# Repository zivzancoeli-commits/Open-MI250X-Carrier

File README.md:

# Open MI250X Carrier

## Purpose
This project collects public evidence needed to design a minimal open-source carrier board for surplus AMD Instinct MI250X OAM modules. It is organized as a reverse-engineering knowledge base: public documentation is collected first, facts are extracted into notes, and unknown or proprietary behavior is tracked instead of assumed.

Agent standing rules: [AGENTS.md](AGENTS.md). Do not invent pins. Do not send in-repo KiCad to PCBWay. Do not energize OAMs. Host / desk / SendCutSend sheet are OK to buy; wait on Molex 2189101115 60 V / skip-pin.

## Workflow
- Collect public links and local reference copies in [02_AMD_Docs](02_AMD_Docs/) and [13_Reference_Docs](13_Reference_Docs/).
- Extract design-relevant facts into [09_AI_Notes](09_AI_Notes/), separating verified information from questions.
- Use research in [08_Research_Papers](08_Research_Papers/) to understand topology, bandwidth, and system context before design decisions.
- Carry verified mechanical, PCIe, power, cooling, firmware, and software assumptions into schematic, layout, prototype, and validation work.

## Top-Level Folders
- [02_AMD_Docs](02_AMD_Docs/): upstream public links for OAM, AMD matrix cores, ROCm compatibility, and MI250X software support.
- [08_Research_Papers](08_Research_Papers/): architecture and data-movement research, currently focused on topology and bandwidth.
- [09_AI_Notes](09_AI_Notes/): topic notes for architecture, PCIe, power, cooling, clocking, management, ideas, questions, and unknowns.
- [13_Reference_Docs](13_Reference_Docs/): local indexes and reference material for AMD, ROCm, OAM/OCP, Molex, cooling, firmware, memory, and components.

## Known Information
- Manual project status items: gather public documentation, understand OAM, identify undocumented interfaces, create architecture, draw schematic, PCB layout, prototype.
- Manual note: undocumented behavior should be tracked as an open question rather than assumed.
- `Wanted_Documents.rtf` tracks OAM, AMD, PCIe, power, cooling, and photo references; no image files are currently present.
- MP2975 is listed as believed present on MI250X, but not visually confirmed.

## Project Roadmap
1. Documentation Collection
2. Knowledge Extraction
3. Reverse Engineering
4. Schematic Design
5. PCB Layout
6. Prototype
7. Bring-up and Validation

## Open Questions
- Mechanical, baseboard, connector, PCIe routing, REFCLK, PMBus, VRM, and OAM thermal references are listed as missing or incomplete.
- Three local PDFs could not be read because they report invalid PDF structure.

## TODO
- Keep `Wanted_Documents.rtf` aligned with files added under `13_Reference_Docs`.
- Move verified findings into `09_AI_Notes` with clear evidence and uncertainty labels.

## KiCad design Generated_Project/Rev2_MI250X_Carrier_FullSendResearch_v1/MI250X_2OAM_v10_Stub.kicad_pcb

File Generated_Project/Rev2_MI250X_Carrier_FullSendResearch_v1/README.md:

# Full-send research v1 — 2× MI250X OAM (NOT fab-ready)

**Copied tree.** Production KiCad under other `Rev2_*` folders was not modified.

**DO NOT FABRICATE. DO NOT ENERGIZE an MI250X on this board.**

A full-send **shopping cart** (host + desk + 2× OAM + Molex + a 48 V brick) is a **buying** decision. It is **not** a PCBWay decision and **not** permission to apply P48V.

This folder advances the v1.0-mapped 2-OAM stub:

- Inner copper: **In1.Cu = P48V**, **In2.Cu = GND** because those names exist on the OCP generic v1.0 map. **P12V1 / P12V2 / P3V3 are not on the 48 V plane.**
- Silk: `DO NOT FABRICATE - DO NOT ENERGIZE OAMs`.
- 8-OAM **keepout** is chassis volume (OCP UBB v1.5 **417 × 585 mm**), not eight electrical seats.
- Unmapped `TEST*` / `RFU` / `DO_NOT_USE` pads still have **no net**.

KiCad **9.0.9** CLI ran ERC and DRC here. The user’s Mac KiCad **10.0.4** can open these files. The board is **not** PCBWay-ready.

## Open these first

| File | What it is |
|---|---|
| [`docs/FULL_SEND_SHOPPING.md`](docs/FULL_SEND_SHOPPING.md) | One cart: A will POST / B sits unused / C do not buy |
| [`docs/BLOCKERS_REMAINING.md`](docs/BLOCKERS_REMAINING.md) | Why PCBWay + plug-in is still forbidden |
| [`docs/RESEARCH_REPORT.md`](docs/RESEARCH_REPORT.md) | Seven research questions, quotes, Verified/Inferred/Unknown |
| [`docs/KICAD_INSTALL.md`](docs/KICAD_INSTALL.md) | How `kicad-cli` got onto this image |
| [`docs/URL_FETCH_LOG.txt`](docs/URL_FETCH_LOG.txt) | HTTP codes for URLs actually retrieved |
| `MI250X_2OAM_v10_Stub.kicad_pro` | KiCad 9 project (4-layer, 2 seats) |

## Regenerate (do not hand-edit pad nets)

```bash
python3 Generated_Project/Rev2_MI250X_Carrier_FullSendResearch_v1/tools/generate_from_v10_pinmap.py
```

If the CSV and the xlsx disagree, **the xlsx wins** (`22_Pinmap_Research/downloads/OAM_Pin_map_rev_1.0.xlsx`).

PR #1 pin map and PR #2 buy-pack are already on `main` (PR #2 merged; PR #1 files are in `22_Pinmap_Research/`). This branch copies forward; it does not overwrite those trees in place.

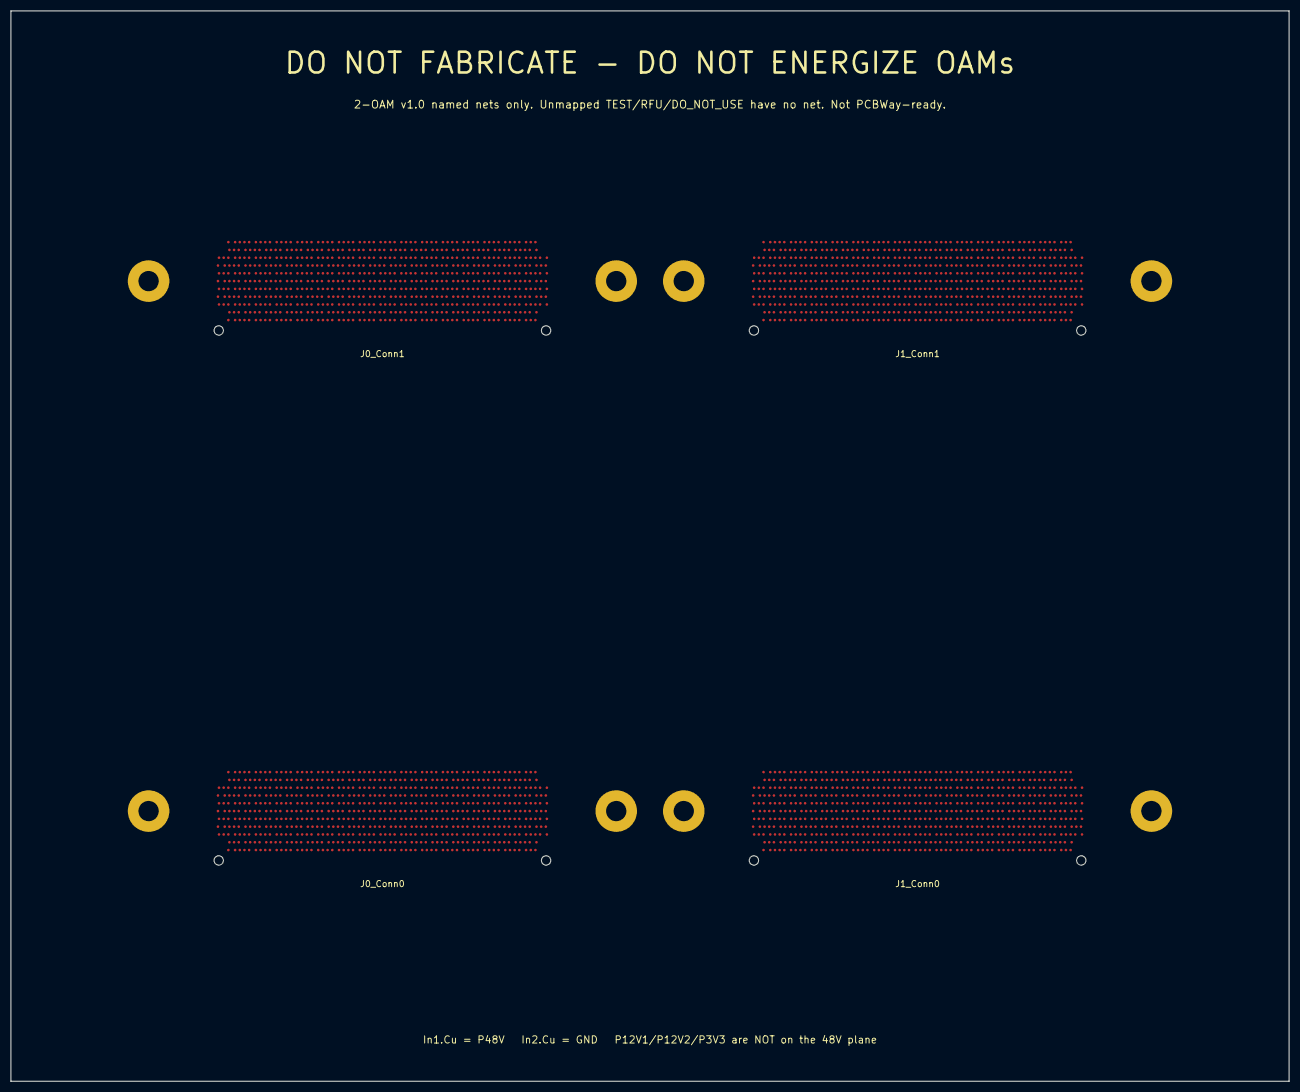
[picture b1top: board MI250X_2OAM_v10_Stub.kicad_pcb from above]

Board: 4 copper layers, 246.0 x 206.0 mm, 12 parts (0 on the bottom side), 7 nets, no tracks yet.

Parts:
H01, H02, H03, H04, H11, H12, H13, H14: NPTH_3.9; NPTH_3.9_Fig2
J0_Conn0, J0_Conn1, J1_Conn0, J1_Conn1: 218910-1115; 218910-1115_candidate

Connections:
GND: J0_Conn0.A5, J0_Conn0.A6, J0_Conn0.A9, J0_Conn0.A10, J0_Conn0.A13, J0_Conn0.A14, J0_Conn0.A17, J0_Conn0.A18, J0_Conn0.A21, J0_Conn0.A22, J0_Conn0.A25, J0_Conn0.A26, J0_Conn0.A29, J0_Conn0.A30, J0_Conn0.A33, J0_Conn0.A34, J0_Conn0.A37, J0_Conn0.A38, J0_Conn0.A41, J0_Conn0.A42, J0_Conn0.A45, J0_Conn0.A46, J0_Conn0.A49, J0_Conn0.A50, J0_Conn0.A53, J0_Conn0.A54, J0_Conn0.A57, J0_Conn0.A58, J0_Conn0.B3, J0_Conn0.B4, J0_Conn0.B7, J0_Conn0.B8, J0_Conn0.B11, J0_Conn0.B12, J0_Conn0.B15, J0_Conn0.B16, J0_Conn0.B19, J0_Conn0.B20, J0_Conn0.B23, J0_Conn0.B24, J0_Conn0.B27, J0_Conn0.B28, J0_Conn0.B31, J0_Conn0.B32, J0_Conn0.B35, J0_Conn0.B36, J0_Conn0.B39, J0_Conn0.B40, J0_Conn0.B43, J0_Conn0.B44, J0_Conn0.B47, J0_Conn0.B48, J0_Conn0.B51, J0_Conn0.B52, J0_Conn0.B55, J0_Conn0.B56, J0_Conn0.B57, J0_Conn0.B58, J0_Conn0.C5, J0_Conn0.C6, J0_Conn0.C9, J0_Conn0.C10, J0_Conn0.C13, J0_Conn0.C14, J0_Conn0.C17, J0_Conn0.C18, J0_Conn0.C21, J0_Conn0.C22, J0_Conn0.C25, J0_Conn0.C26, J0_Conn0.C29, J0_Conn0.C30, J0_Conn0.C33, J0_Conn0.C34, J0_Conn0.C37, J0_Conn0.C38, J0_Conn0.C41, J0_Conn0.C42, J0_Conn0.C45, J0_Conn0.C46, J0_Conn0.C49, J0_Conn0.C50, J0_Conn0.C53, J0_Conn0.C54, J0_Conn0.C57, J0_Conn0.C58, J0_Conn0.D3, J0_Conn0.D4, J0_Conn0.D7, J0_Conn0.D8, J0_Conn0.D11, J0_Conn0.D12, J0_Conn0.D15, J0_Conn0.D16, J0_Conn0.D19, J0_Conn0.D20, J0_Conn0.D23, J0_Conn0.D24, J0_Conn0.D27, J0_Conn0.D28, J0_Conn0.D31, J0_Conn0.D32, J0_Conn0.D35, J0_Conn0.D36, J0_Conn0.D39, J0_Conn0.D40, J0_Conn0.D43, J0_Conn0.D44, J0_Conn0.D47, J0_Conn0.D48, J0_Conn0.D51, J0_Conn0.D52, J0_Conn0.D55, J0_Conn0.D56, J0_Conn0.D57, J0_Conn0.D58, J0_Conn0.E1, J0_Conn0.E2, J0_Conn0.E5, J0_Conn0.E6, J0_Conn0.E9, J0_Conn0.E10, J0_Conn0.E13, J0_Conn0.E14, J0_Conn0.E17, J0_Conn0.E18, J0_Conn0.E21, J0_Conn0.E22, J0_Conn0.E25, J0_Conn0.E26, J0_Conn0.E29, J0_Conn0.E30, J0_Conn0.E33, J0_Conn0.E34, J0_Conn0.E37, J0_Conn0.E38, J0_Conn0.E41, J0_Conn0.E42, J0_Conn0.E45, J0_Conn0.E46, J0_Conn0.E49, J0_Conn0.E50, J0_Conn0.E53, J0_Conn0.E54, J0_Conn0.E55, J0_Conn0.E56, J0_Conn0.E57, J0_Conn0.E58, J0_Conn0.F3, J0_Conn0.F4, J0_Conn0.F7, J0_Conn0.F8, J0_Conn0.F11, J0_Conn0.F12, J0_Conn0.F15, J0_Conn0.F16, J0_Conn0.F19, J0_Conn0.F20, J0_Conn0.F23, J0_Conn0.F24, J0_Conn0.F27, J0_Conn0.F28, J0_Conn0.F31, J0_Conn0.F32, J0_Conn0.F35, J0_Conn0.F36, J0_Conn0.F39, J0_Conn0.F40, J0_Conn0.F43, J0_Conn0.F44, J0_Conn0.F47, J0_Conn0.F48, J0_Conn0.F51, J0_Conn0.F52, J0_Conn0.F53, J0_Conn0.F54, J0_Conn0.F55, J0_Conn0.F56, J0_Conn0.F57, J0_Conn0.F58, J0_Conn0.G5, J0_Conn0.G6, J0_Conn0.G9, J0_Conn0.G10, J0_Conn0.G13, J0_Conn0.G14, J0_Conn0.G17, J0_Conn0.G18, J0_Conn0.G21, J0_Conn0.G22, J0_Conn0.G25, J0_Conn0.G26, J0_Conn0.G29, J0_Conn0.G30, J0_Conn0.G33, J0_Conn0.G34, J0_Conn0.G37, J0_Conn0.G38, J0_Conn0.G41, J0_Conn0.G42, J0_Conn0.G45, J0_Conn0.G46, J0_Conn0.G49, J0_Conn0.G50, J0_Conn0.G53, J0_Conn0.G54, J0_Conn0.G55, J0_Conn0.G56, J0_Conn0.G57, J0_Conn0.G58, J0_Conn0.G59, J0_Conn0.G60, J0_Conn0.G61, J0_Conn0.G62, J0_Conn0.G63, J0_Conn0.G64, J0_Conn0.H3, J0_Conn0.H4, J0_Conn0.H7, J0_Conn0.H8, J0_Conn0.H11, J0_Conn0.H12, J0_Conn0.H15, J0_Conn0.H16, J0_Conn0.H19, J0_Conn0.H20, J0_Conn0.H23, J0_Conn0.H24, J0_Conn0.H27, J0_Conn0.H28, J0_Conn0.H31, J0_Conn0.H32, J0_Conn0.H35, J0_Conn0.H36, J0_Conn0.H39, J0_Conn0.H40, J0_Conn0.H43, J0_Conn0.H44, J0_Conn0.H47, J0_Conn0.H48, J0_Conn0.H51, J0_Conn0.H52, J0_Conn0.H55, J0_Conn0.H56, J0_Conn0.H57, J0_Conn0.J1, J0_Conn0.J2, J0_Conn0.J5, J0_Conn0.J6, J0_Conn0.J9, J0_Conn0.J10, J0_Conn0.J13, J0_Conn0.J14, J0_Conn0.J17, J0_Conn0.J18, J0_Conn0.J21, J0_Conn0.J22, J0_Conn0.J25, J0_Conn0.J26, J0_Conn0.J29, J0_Conn0.J30, J0_Conn0.J33, J0_Conn0.J34, J0_Conn0.J37, J0_Conn0.J38, J0_Conn0.J41, J0_Conn0.J42, J0_Conn0.J45, J0_Conn0.J46, J0_Conn0.J49, J0_Conn0.J50, J0_Conn0.J53, J0_Conn0.J54, J0_Conn0.J57, J0_Conn0.J58, J0_Conn0.J59, J0_Conn0.K3, J0_Conn0.K4, J0_Conn0.K7, J0_Conn0.K8, J0_Conn0.K11, J0_Conn0.K12, J0_Conn0.K15, J0_Conn0.K16, J0_Conn0.K19, J0_Conn0.K20, J0_Conn0.K23, J0_Conn0.K24, J0_Conn0.K27, J0_Conn0.K28, J0_Conn0.K31, J0_Conn0.K32, J0_Conn0.K35, J0_Conn0.K36, J0_Conn0.K39, J0_Conn0.K40, J0_Conn0.K43, J0_Conn0.K44, J0_Conn0.K47, J0_Conn0.K48, J0_Conn0.K51, J0_Conn0.K52, J0_Conn0.K55, J0_Conn0.K56, J0_Conn0.K57, J0_Conn0.L5, J0_Conn0.L6, J0_Conn0.L9, J0_Conn0.L10, J0_Conn0.L13, J0_Conn0.L14, J0_Conn0.L17, J0_Conn0.L18, J0_Conn0.L21, J0_Conn0.L22, J0_Conn0.L25, J0_Conn0.L26, J0_Conn0.L29, J0_Conn0.L30, J0_Conn0.L33, J0_Conn0.L34, J0_Conn0.L37, J0_Conn0.L38, J0_Conn0.L41, J0_Conn0.L42, J0_Conn0.L45, J0_Conn0.L46, J0_Conn0.L49, J0_Conn0.L50, J0_Conn0.L53, J0_Conn0.L54, J0_Conn0.L57, J0_Conn0.L58, J0_Conn0.L59, J0_Conn1.A5, J0_Conn1.A6, J0_Conn1.A9, J0_Conn1.A10, J0_Conn1.A13, J0_Conn1.A14, J0_Conn1.A17, J0_Conn1.A18, J0_Conn1.A21, J0_Conn1.A22, J0_Conn1.A25, J0_Conn1.A26, J0_Conn1.A29, J0_Conn1.A30, J0_Conn1.A33, J0_Conn1.A34, J0_Conn1.A37, J0_Conn1.A38, J0_Conn1.A41, J0_Conn1.A42, J0_Conn1.A45, J0_Conn1.A46, J0_Conn1.A49, J0_Conn1.A50, J0_Conn1.A53, J0_Conn1.A54, J0_Conn1.A57, J0_Conn1.A58, J0_Conn1.A61, J0_Conn1.A62, J0_Conn1.B3, J0_Conn1.B4, J0_Conn1.B7, J0_Conn1.B8, J0_Conn1.B11, J0_Conn1.B12, J0_Conn1.B15, J0_Conn1.B16, J0_Conn1.B19, J0_Conn1.B20, J0_Conn1.B23, J0_Conn1.B24, J0_Conn1.B27, J0_Conn1.B28, J0_Conn1.B31, J0_Conn1.B32, J0_Conn1.B35, J0_Conn1.B36, J0_Conn1.B39, J0_Conn1.B40, J0_Conn1.B43, J0_Conn1.B44, J0_Conn1.B47, J0_Conn1.B48, J0_Conn1.B51, J0_Conn1.B52, J0_Conn1.B55, J0_Conn1.B56, J0_Conn1.B59, J0_Conn1.B60, J0_Conn1.C1, J0_Conn1.C2, J0_Conn1.C5, J0_Conn1.C6, J0_Conn1.C9, J0_Conn1.C10, J0_Conn1.C13, J0_Conn1.C14, J0_Conn1.C17, J0_Conn1.C18, J0_Conn1.C21, J0_Conn1.C22, J0_Conn1.C25, J0_Conn1.C26, J0_Conn1.C29, J0_Conn1.C30, J0_Conn1.C33, J0_Conn1.C34, J0_Conn1.C37, J0_Conn1.C38, J0_Conn1.C41, J0_Conn1.C42, J0_Conn1.C45, J0_Conn1.C46, J0_Conn1.C49, J0_Conn1.C50, J0_Conn1.C53, J0_Conn1.C54, J0_Conn1.C57, J0_Conn1.C58, J0_Conn1.C61, J0_Conn1.C62, J0_Conn1.D3, J0_Conn1.D4, J0_Conn1.D7, J0_Conn1.D8, J0_Conn1.D11, J0_Conn1.D12, J0_Conn1.D15, J0_Conn1.D16, J0_Conn1.D19, J0_Conn1.D20, J0_Conn1.D23, J0_Conn1.D24, J0_Conn1.D27, J0_Conn1.D28, J0_Conn1.D31, J0_Conn1.D32, J0_Conn1.D35, J0_Conn1.D36, J0_Conn1.D39, J0_Conn1.D40, J0_Conn1.D43, J0_Conn1.D44, J0_Conn1.D47, J0_Conn1.D48, J0_Conn1.D51, J0_Conn1.D52, J0_Conn1.D55, J0_Conn1.D56, J0_Conn1.D59, J0_Conn1.D60, J0_Conn1.D63, J0_Conn1.D64, J0_Conn1.E1, J0_Conn1.E2, J0_Conn1.E5, J0_Conn1.E6, J0_Conn1.E9, J0_Conn1.E10, J0_Conn1.E13, J0_Conn1.E14, J0_Conn1.E17, J0_Conn1.E18, J0_Conn1.E21, J0_Conn1.E22, J0_Conn1.E25, J0_Conn1.E26, J0_Conn1.E29, J0_Conn1.E30, J0_Conn1.E33, J0_Conn1.E34, J0_Conn1.E37, J0_Conn1.E38, J0_Conn1.E41, J0_Conn1.E42, J0_Conn1.E45, J0_Conn1.E46, J0_Conn1.E49, J0_Conn1.E50, J0_Conn1.E53, J0_Conn1.E54, J0_Conn1.E57, J0_Conn1.E58, J0_Conn1.E61, J0_Conn1.E62, J0_Conn1.F3, J0_Conn1.F4, J0_Conn1.F7, J0_Conn1.F8, J0_Conn1.F11, J0_Conn1.F12, J0_Conn1.F15, J0_Conn1.F16, J0_Conn1.F19, J0_Conn1.F20, J0_Conn1.F23, J0_Conn1.F24, J0_Conn1.F27, J0_Conn1.F28, J0_Conn1.F31, J0_Conn1.F32, J0_Conn1.F35, J0_Conn1.F36, J0_Conn1.F39, J0_Conn1.F40, J0_Conn1.F43, J0_Conn1.F44, J0_Conn1.F47, J0_Conn1.F48, J0_Conn1.F51, J0_Conn1.F52, J0_Conn1.F55, J0_Conn1.F56, J0_Conn1.F59, J0_Conn1.F60, J0_Conn1.F63, J0_Conn1.F64, J0_Conn1.G1, J0_Conn1.G2, J0_Conn1.G5, J0_Conn1.G6, J0_Conn1.G9, J0_Conn1.G10, J0_Conn1.G13, J0_Conn1.G14, J0_Conn1.G17, J0_Conn1.G18, J0_Conn1.G21, J0_Conn1.G22, J0_Conn1.G25, J0_Conn1.G26, J0_Conn1.G29, J0_Conn1.G30, J0_Conn1.G33, J0_Conn1.G34, J0_Conn1.G37, J0_Conn1.G38, J0_Conn1.G41, J0_Conn1.G42, J0_Conn1.G45, J0_Conn1.G46, J0_Conn1.G49, J0_Conn1.G50, J0_Conn1.G53, J0_Conn1.G54, J0_Conn1.G57, J0_Conn1.G58, J0_Conn1.G61, J0_Conn1.G62, J0_Conn1.H3, J0_Conn1.H4, J0_Conn1.H7, J0_Conn1.H8, J0_Conn1.H11, J0_Conn1.H12, J0_Conn1.H15, J0_Conn1.H16, J0_Conn1.H19, J0_Conn1.H20, J0_Conn1.H23, J0_Conn1.H24, J0_Conn1.H27, J0_Conn1.H28, J0_Conn1.H31, J0_Conn1.H32, J0_Conn1.H35, J0_Conn1.H36, J0_Conn1.H39, J0_Conn1.H40, J0_Conn1.H43, J0_Conn1.H44, J0_Conn1.H47, J0_Conn1.H48, J0_Conn1.H51, J0_Conn1.H52, J0_Conn1.H55, J0_Conn1.H56, J0_Conn1.H59, J0_Conn1.H60, J0_Conn1.H63, J0_Conn1.H64, J0_Conn1.J1, J0_Conn1.J2, J0_Conn1.J5, J0_Conn1.J6, J0_Conn1.J9, J0_Conn1.J10, J0_Conn1.J13, J0_Conn1.J14, J0_Conn1.J17, J0_Conn1.J18, J0_Conn1.J21, J0_Conn1.J22, J0_Conn1.J25, J0_Conn1.J26, J0_Conn1.J29, J0_Conn1.J30, J0_Conn1.J33, J0_Conn1.J34, J0_Conn1.J37, J0_Conn1.J38, J0_Conn1.J41, J0_Conn1.J42, J0_Conn1.J45, J0_Conn1.J46, J0_Conn1.J49, J0_Conn1.J50, J0_Conn1.J53, J0_Conn1.J54, J0_Conn1.J57, J0_Conn1.J58, J0_Conn1.J61, J0_Conn1.J62, J0_Conn1.K3, J0_Conn1.K4, J0_Conn1.K7, J0_Conn1.K8, J0_Conn1.K11, J0_Conn1.K12, J0_Conn1.K15, J0_Conn1.K16, J0_Conn1.K19, J0_Conn1.K20, J0_Conn1.K23, J0_Conn1.K24, J0_Conn1.K27, J0_Conn1.K28, J0_Conn1.K31, J0_Conn1.K32, J0_Conn1.K35, J0_Conn1.K36, J0_Conn1.K39, J0_Conn1.K40, J0_Conn1.K43, J0_Conn1.K44, J0_Conn1.K47, J0_Conn1.K48, J0_Conn1.K51, J0_Conn1.K52, J0_Conn1.K55, J0_Conn1.K56, J0_Conn1.K59, J0_Conn1.K60, J0_Conn1.L5, J0_Conn1.L6, J0_Conn1.L9, J0_Conn1.L10, J0_Conn1.L13, J0_Conn1.L14, J0_Conn1.L17, J0_Conn1.L18, J0_Conn1.L21, J0_Conn1.L22, J0_Conn1.L25, J0_Conn1.L26, J0_Conn1.L29, J0_Conn1.L30, J0_Conn1.L33, J0_Conn1.L34, J0_Conn1.L37, J0_Conn1.L38, J0_Conn1.L41, J0_Conn1.L42, J0_Conn1.L45, J0_Conn1.L46, J0_Conn1.L49, J0_Conn1.L50, J0_Conn1.L53, J0_Conn1.L54, J0_Conn1.L57, J0_Conn1.L58, J0_Conn1.L61, J0_Conn1.L62, J1_Conn0.A5, J1_Conn0.A6, J1_Conn0.A9, J1_Conn0.A10, J1_Conn0.A13, J1_Conn0.A14, J1_Conn0.A17, J1_Conn0.A18, J1_Conn0.A21, J1_Conn0.A22, J1_Conn0.A25, J1_Conn0.A26, J1_Conn0.A29, J1_Conn0.A30, J1_Conn0.A33, J1_Conn0.A34, J1_Conn0.A37, J1_Conn0.A38, J1_Conn0.A41, J1_Conn0.A42, J1_Conn0.A45, J1_Conn0.A46, J1_Conn0.A49, J1_Conn0.A50, J1_Conn0.A53, J1_Conn0.A54, J1_Conn0.A57, J1_Conn0.A58, J1_Conn0.B3, J1_Conn0.B4, J1_Conn0.B7, J1_Conn0.B8, J1_Conn0.B11, J1_Conn0.B12, J1_Conn0.B15, J1_Conn0.B16, J1_Conn0.B19, J1_Conn0.B20, J1_Conn0.B23, J1_Conn0.B24, J1_Conn0.B27, J1_Conn0.B28, J1_Conn0.B31, J1_Conn0.B32, J1_Conn0.B35, J1_Conn0.B36, J1_Conn0.B39, J1_Conn0.B40, J1_Conn0.B43, J1_Conn0.B44, J1_Conn0.B47, J1_Conn0.B48, J1_Conn0.B51, J1_Conn0.B52, J1_Conn0.B55, J1_Conn0.B56, J1_Conn0.B57, J1_Conn0.B58, J1_Conn0.C5, J1_Conn0.C6, J1_Conn0.C9, J1_Conn0.C10, J1_Conn0.C13, J1_Conn0.C14, J1_Conn0.C17, J1_Conn0.C18, J1_Conn0.C21, J1_Conn0.C22, J1_Conn0.C25, J1_Conn0.C26, J1_Conn0.C29, J1_Conn0.C30, J1_Conn0.C33, J1_Conn0.C34, J1_Conn0.C37, J1_Conn0.C38, J1_Conn0.C41, J1_Conn0.C42, J1_Conn0.C45, J1_Conn0.C46, J1_Conn0.C49, J1_Conn0.C50, J1_Conn0.C53, J1_Conn0.C54, J1_Conn0.C57, J1_Conn0.C58, J1_Conn0.D3, J1_Conn0.D4, J1_Conn0.D7, J1_Conn0.D8, J1_Conn0.D11, J1_Conn0.D12, J1_Conn0.D15, J1_Conn0.D16, J1_Conn0.D19, J1_Conn0.D20, J1_Conn0.D23, J1_Conn0.D24, J1_Conn0.D27, J1_Conn0.D28, J1_Conn0.D31, J1_Conn0.D32, J1_Conn0.D35, J1_Conn0.D36, J1_Conn0.D39, J1_Conn0.D40, J1_Conn0.D43, J1_Conn0.D44, J1_Conn0.D47, J1_Conn0.D48, J1_Conn0.D51, J1_Conn0.D52, J1_Conn0.D55, J1_Conn0.D56, J1_Conn0.D57, J1_Conn0.D58, J1_Conn0.E1, J1_Conn0.E2, J1_Conn0.E5, J1_Conn0.E6, J1_Conn0.E9, J1_Conn0.E10, J1_Conn0.E13, J1_Conn0.E14, J1_Conn0.E17, J1_Conn0.E18, J1_Conn0.E21, J1_Conn0.E22, J1_Conn0.E25, J1_Conn0.E26, J1_Conn0.E29, J1_Conn0.E30, J1_Conn0.E33, J1_Conn0.E34, J1_Conn0.E37, J1_Conn0.E38, J1_Conn0.E41, J1_Conn0.E42, J1_Conn0.E45, J1_Conn0.E46, J1_Conn0.E49, J1_Conn0.E50, J1_Conn0.E53, J1_Conn0.E54, J1_Conn0.E55, J1_Conn0.E56, J1_Conn0.E57, J1_Conn0.E58, J1_Conn0.F3, J1_Conn0.F4, J1_Conn0.F7, J1_Conn0.F8, J1_Conn0.F11, J1_Conn0.F12, J1_Conn0.F15, J1_Conn0.F16, J1_Conn0.F19, J1_Conn0.F20, J1_Conn0.F23, J1_Conn0.F24, J1_Conn0.F27, J1_Conn0.F28, J1_Conn0.F31, J1_Conn0.F32, J1_Conn0.F35, J1_Conn0.F36, J1_Conn0.F39, J1_Conn0.F40, J1_Conn0.F43, J1_Conn0.F44, J1_Conn0.F47, J1_Conn0.F48, J1_Conn0.F51, J1_Conn0.F52, J1_Conn0.F53, J1_Conn0.F54, J1_Conn0.F55, J1_Conn0.F56, J1_Conn0.F57, J1_Conn0.F58, J1_Conn0.G5, J1_Conn0.G6, J1_Conn0.G9, J1_Conn0.G10, J1_Conn0.G13, J1_Conn0.G14, J1_Conn0.G17, J1_Conn0.G18, J1_Conn0.G21, J1_Conn0.G22, J1_Conn0.G25, J1_Conn0.G26, J1_Conn0.G29, J1_Conn0.G30, J1_Conn0.G33, J1_Conn0.G34, J1_Conn0.G37, J1_Conn0.G38, J1_Conn0.G41, J1_Conn0.G42, J1_Conn0.G45, J1_Conn0.G46, J1_Conn0.G49, J1_Conn0.G50, J1_Conn0.G53, J1_Conn0.G54, J1_Conn0.G55, J1_Conn0.G56, J1_Conn0.G57, J1_Conn0.G58, J1_Conn0.G59, J1_Conn0.G60, J1_Conn0.G61, J1_Conn0.G62, J1_Conn0.G63, J1_Conn0.G64, J1_Conn0.H3, J1_Conn0.H4, J1_Conn0.H7, J1_Conn0.H8, J1_Conn0.H11, J1_Conn0.H12, J1_Conn0.H15, J1_Conn0.H16, J1_Conn0.H19, J1_Conn0.H20, J1_Conn0.H23, J1_Conn0.H24, J1_Conn0.H27, J1_Conn0.H28, J1_Conn0.H31, J1_Conn0.H32, J1_Conn0.H35, J1_Conn0.H36, J1_Conn0.H39, J1_Conn0.H40, J1_Conn0.H43, J1_Conn0.H44, J1_Conn0.H47, J1_Conn0.H48, J1_Conn0.H51, J1_Conn0.H52, J1_Conn0.H55, J1_Conn0.H56, J1_Conn0.H57, J1_Conn0.J1, J1_Conn0.J2, J1_Conn0.J5, J1_Conn0.J6, J1_Conn0.J9, J1_Conn0.J10, J1_Conn0.J13, J1_Conn0.J14, J1_Conn0.J17, J1_Conn0.J18, J1_Conn0.J21, J1_Conn0.J22, J1_Conn0.J25, J1_Conn0.J26, J1_Conn0.J29, J1_Conn0.J30, J1_Conn0.J33, J1_Conn0.J34, J1_Conn0.J37, J1_Conn0.J38, J1_Conn0.J41, J1_Conn0.J42, J1_Conn0.J45, J1_Conn0.J46, J1_Conn0.J49, J1_Conn0.J50, J1_Conn0.J53, J1_Conn0.J54, J1_Conn0.J57, J1_Conn0.J58, J1_Conn0.J59, J1_Conn0.K3, J1_Conn0.K4, J1_Conn0.K7, J1_Conn0.K8, J1_Conn0.K11, J1_Conn0.K12, J1_Conn0.K15, J1_Conn0.K16, J1_Conn0.K19, J1_Conn0.K20, J1_Conn0.K23, J1_Conn0.K24, J1_Conn0.K27, J1_Conn0.K28, J1_Conn0.K31, J1_Conn0.K32, J1_Conn0.K35, J1_Conn0.K36, J1_Conn0.K39, J1_Conn0.K40, J1_Conn0.K43, J1_Conn0.K44, J1_Conn0.K47, J1_Conn0.K48, J1_Conn0.K51, J1_Conn0.K52, J1_Conn0.K55, J1_Conn0.K56, J1_Conn0.K57, J1_Conn0.L5, J1_Conn0.L6, J1_Conn0.L9, J1_Conn0.L10, J1_Conn0.L13, J1_Conn0.L14, J1_Conn0.L17, J1_Conn0.L18, J1_Conn0.L21, J1_Conn0.L22, J1_Conn0.L25, J1_Conn0.L26, J1_Conn0.L29, J1_Conn0.L30, J1_Conn0.L33, J1_Conn0.L34, J1_Conn0.L37, J1_Conn0.L38, J1_Conn0.L41, J1_Conn0.L42, J1_Conn0.L45, J1_Conn0.L46, J1_Conn0.L49, J1_Conn0.L50, J1_Conn0.L53, J1_Conn0.L54, J1_Conn0.L57, J1_Conn0.L58, J1_Conn0.L59, J1_Conn1.A5, J1_Conn1.A6, J1_Conn1.A9, J1_Conn1.A10, J1_Conn1.A13, J1_Conn1.A14, J1_Conn1.A17, J1_Conn1.A18, J1_Conn1.A21, J1_Conn1.A22, J1_Conn1.A25, J1_Conn1.A26, J1_Conn1.A29, J1_Conn1.A30, J1_Conn1.A33, J1_Conn1.A34, J1_Conn1.A37, J1_Conn1.A38, J1_Conn1.A41, J1_Conn1.A42, J1_Conn1.A45, J1_Conn1.A46, J1_Conn1.A49, J1_Conn1.A50, J1_Conn1.A53, J1_Conn1.A54, J1_Conn1.A57, J1_Conn1.A58, J1_Conn1.A61, J1_Conn1.A62, J1_Conn1.B3, J1_Conn1.B4, J1_Conn1.B7, J1_Conn1.B8, J1_Conn1.B11, J1_Conn1.B12, J1_Conn1.B15, J1_Conn1.B16, J1_Conn1.B19, J1_Conn1.B20, J1_Conn1.B23, J1_Conn1.B24, J1_Conn1.B27, J1_Conn1.B28, J1_Conn1.B31, J1_Conn1.B32, J1_Conn1.B35, J1_Conn1.B36, J1_Conn1.B39, J1_Conn1.B40, J1_Conn1.B43, J1_Conn1.B44, J1_Conn1.B47, J1_Conn1.B48, J1_Conn1.B51, J1_Conn1.B52, J1_Conn1.B55, J1_Conn1.B56, J1_Conn1.B59, J1_Conn1.B60, J1_Conn1.C1, J1_Conn1.C2, J1_Conn1.C5, J1_Conn1.C6, J1_Conn1.C9, J1_Conn1.C10, J1_Conn1.C13, J1_Conn1.C14, J1_Conn1.C17, J1_Conn1.C18, J1_Conn1.C21, J1_Conn1.C22, J1_Conn1.C25, J1_Conn1.C26, J1_Conn1.C29, J1_Conn1.C30, J1_Conn1.C33, J1_Conn1.C34, J1_Conn1.C37, J1_Conn1.C38, J1_Conn1.C41, J1_Conn1.C42, J1_Conn1.C45, J1_Conn1.C46, J1_Conn1.C49, J1_Conn1.C50, J1_Conn1.C53, J1_Conn1.C54, J1_Conn1.C57, J1_Conn1.C58, J1_Conn1.C61, J1_Conn1.C62, J1_Conn1.D3, J1_Conn1.D4, J1_Conn1.D7, J1_Conn1.D8, J1_Conn1.D11, J1_Conn1.D12, J1_Conn1.D15, J1_Conn1.D16, J1_Conn1.D19, J1_Conn1.D20, J1_Conn1.D23, J1_Conn1.D24, J1_Conn1.D27, J1_Conn1.D28, J1_Conn1.D31, J1_Conn1.D32, J1_Conn1.D35, J1_Conn1.D36, J1_Conn1.D39, J1_Conn1.D40, J1_Conn1.D43, J1_Conn1.D44, J1_Conn1.D47, J1_Conn1.D48, J1_Conn1.D51, J1_Conn1.D52, J1_Conn1.D55, J1_Conn1.D56, J1_Conn1.D59, J1_Conn1.D60, J1_Conn1.D63, J1_Conn1.D64, J1_Conn1.E1, J1_Conn1.E2, J1_Conn1.E5, J1_Conn1.E6, J1_Conn1.E9, J1_Conn1.E10, J1_Conn1.E13, J1_Conn1.E14, J1_Conn1.E17, J1_Conn1.E18, J1_Conn1.E21, J1_Conn1.E22, J1_Conn1.E25, J1_Conn1.E26, J1_Conn1.E29, J1_Conn1.E30, J1_Conn1.E33, J1_Conn1.E34, J1_Conn1.E37, J1_Conn1.E38, J1_Conn1.E41, J1_Conn1.E42, J1_Conn1.E45, J1_Conn1.E46, J1_Conn1.E49, J1_Conn1.E50, J1_Conn1.E53, J1_Conn1.E54, J1_Conn1.E57, J1_Conn1.E58, J1_Conn1.E61, J1_Conn1.E62, J1_Conn1.F3, J1_Conn1.F4, J1_Conn1.F7, J1_Conn1.F8, J1_Conn1.F11, J1_Conn1.F12, J1_Conn1.F15, J1_Conn1.F16, J1_Conn1.F19, J1_Conn1.F20, J1_Conn1.F23, J1_Conn1.F24, J1_Conn1.F27, J1_Conn1.F28, J1_Conn1.F31, J1_Conn1.F32, J1_Conn1.F35, J1_Conn1.F36, J1_Conn1.F39, J1_Conn1.F40, J1_Conn1.F43, J1_Conn1.F44, J1_Conn1.F47, J1_Conn1.F48, J1_Conn1.F51, J1_Conn1.F52, J1_Conn1.F55, J1_Conn1.F56, J1_Conn1.F59, J1_Conn1.F60, J1_Conn1.F63, J1_Conn1.F64, J1_Conn1.G1, J1_Conn1.G2, J1_Conn1.G5, J1_Conn1.G6, J1_Conn1.G9, J1_Conn1.G10, J1_Conn1.G13, J1_Conn1.G14, J1_Conn1.G17, J1_Conn1.G18, J1_Conn1.G21, J1_Conn1.G22, J1_Conn1.G25, J1_Conn1.G26, J1_Conn1.G29, J1_Conn1.G30, J1_Conn1.G33, J1_Conn1.G34, J1_Conn1.G37, J1_Conn1.G38, J1_Conn1.G41, J1_Conn1.G42, J1_Conn1.G45, J1_Conn1.G46, J1_Conn1.G49, J1_Conn1.G50, J1_Conn1.G53, J1_Conn1.G54, J1_Conn1.G57, J1_Conn1.G58, J1_Conn1.G61, J1_Conn1.G62, J1_Conn1.H3, J1_Conn1.H4, J1_Conn1.H7, J1_Conn1.H8, J1_Conn1.H11, J1_Conn1.H12, J1_Conn1.H15, J1_Conn1.H16, J1_Conn1.H19, J1_Conn1.H20, J1_Conn1.H23, J1_Conn1.H24, J1_Conn1.H27, J1_Conn1.H28, J1_Conn1.H31, J1_Conn1.H32, J1_Conn1.H35, J1_Conn1.H36, J1_Conn1.H39, J1_Conn1.H40, J1_Conn1.H43, J1_Conn1.H44, J1_Conn1.H47, J1_Conn1.H48, J1_Conn1.H51, J1_Conn1.H52, J1_Conn1.H55, J1_Conn1.H56, J1_Conn1.H59, J1_Conn1.H60, J1_Conn1.H63, J1_Conn1.H64, J1_Conn1.J1, J1_Conn1.J2, J1_Conn1.J5, J1_Conn1.J6, J1_Conn1.J9, J1_Conn1.J10, J1_Conn1.J13, J1_Conn1.J14, J1_Conn1.J17, J1_Conn1.J18, J1_Conn1.J21, J1_Conn1.J22, J1_Conn1.J25, J1_Conn1.J26, J1_Conn1.J29, J1_Conn1.J30, J1_Conn1.J33, J1_Conn1.J34, J1_Conn1.J37, J1_Conn1.J38, J1_Conn1.J41, J1_Conn1.J42, J1_Conn1.J45, J1_Conn1.J46, J1_Conn1.J49, J1_Conn1.J50, J1_Conn1.J53, J1_Conn1.J54, J1_Conn1.J57, J1_Conn1.J58, J1_Conn1.J61, J1_Conn1.J62, J1_Conn1.K3, J1_Conn1.K4, J1_Conn1.K7, J1_Conn1.K8, J1_Conn1.K11, J1_Conn1.K12, J1_Conn1.K15, J1_Conn1.K16, J1_Conn1.K19, J1_Conn1.K20, J1_Conn1.K23, J1_Conn1.K24, J1_Conn1.K27, J1_Conn1.K28, J1_Conn1.K31, J1_Conn1.K32, J1_Conn1.K35, J1_Conn1.K36, J1_Conn1.K39, J1_Conn1.K40, J1_Conn1.K43, J1_Conn1.K44, J1_Conn1.K47, J1_Conn1.K48, J1_Conn1.K51, J1_Conn1.K52, J1_Conn1.K55, J1_Conn1.K56, J1_Conn1.K59, J1_Conn1.K60, J1_Conn1.L5, J1_Conn1.L6, J1_Conn1.L9, J1_Conn1.L10, J1_Conn1.L13, J1_Conn1.L14, J1_Conn1.L17, J1_Conn1.L18, J1_Conn1.L21, J1_Conn1.L22, J1_Conn1.L25, J1_Conn1.L26, J1_Conn1.L29, J1_Conn1.L30, J1_Conn1.L33, J1_Conn1.L34, J1_Conn1.L37, J1_Conn1.L38, J1_Conn1.L41, J1_Conn1.L42, J1_Conn1.L45, J1_Conn1.L46, J1_Conn1.L49, J1_Conn1.L50, J1_Conn1.L53, J1_Conn1.L54, J1_Conn1.L57, J1_Conn1.L58, J1_Conn1.L61, J1_Conn1.L62
OAM0_PVREF: J0_Conn0.G1, J0_Conn0.G2
OAM1_PVREF: J1_Conn0.G1, J1_Conn0.G2
P3V3: J0_Conn0.C1, J0_Conn0.C2, J1_Conn0.C1, J1_Conn0.C2
P12V1: J0_Conn0.A59, J0_Conn0.A60, J0_Conn0.A61, J0_Conn0.A62, J0_Conn0.B62, J1_Conn0.A59, J1_Conn0.A60, J1_Conn0.A61, J1_Conn0.A62, J1_Conn0.B62
P12V2: J0_Conn0.B59, J0_Conn0.B60, J0_Conn0.B61, J0_Conn0.C59, J0_Conn0.C60, J0_Conn0.C61, J0_Conn0.C62, J0_Conn0.C63, J0_Conn0.C64, J0_Conn0.D59, J0_Conn0.D60, J0_Conn0.D61, J0_Conn0.D62, J0_Conn0.D63, J0_Conn0.D64, J0_Conn0.E59, J0_Conn0.E60, J0_Conn0.E61, J0_Conn0.E62, J0_Conn0.E63, J0_Conn0.E64, J0_Conn0.F59, J0_Conn0.F60, J0_Conn0.F61, J0_Conn0.F62, J0_Conn0.F63, J0_Conn0.F64, J1_Conn0.B59, J1_Conn0.B60, J1_Conn0.B61, J1_Conn0.C59, J1_Conn0.C60, J1_Conn0.C61, J1_Conn0.C62, J1_Conn0.C63, J1_Conn0.C64, J1_Conn0.D59, J1_Conn0.D60, J1_Conn0.D61, J1_Conn0.D62, J1_Conn0.D63, J1_Conn0.D64, J1_Conn0.E59, J1_Conn0.E60, J1_Conn0.E61, J1_Conn0.E62, J1_Conn0.E63, J1_Conn0.E64, J1_Conn0.F59, J1_Conn0.F60, J1_Conn0.F61, J1_Conn0.F62, J1_Conn0.F63, J1_Conn0.F64
P48V: J0_Conn0.H59, J0_Conn0.H60, J0_Conn0.H61, J0_Conn0.H62, J0_Conn0.H63, J0_Conn0.H64, J0_Conn0.J61, J0_Conn0.J62, J0_Conn0.J63, J0_Conn0.J64, J0_Conn0.K59, J0_Conn0.K60, J0_Conn0.K61, J0_Conn0.K62, J0_Conn0.L61, J0_Conn0.L62, J1_Conn0.H59, J1_Conn0.H60, J1_Conn0.H61, J1_Conn0.H62, J1_Conn0.H63, J1_Conn0.H64, J1_Conn0.J61, J1_Conn0.J62, J1_Conn0.J63, J1_Conn0.J64, J1_Conn0.K59, J1_Conn0.K60, J1_Conn0.K61, J1_Conn0.K62, J1_Conn0.L61, J1_Conn0.L62

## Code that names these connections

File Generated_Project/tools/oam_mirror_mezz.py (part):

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        "conn1_todo_placeholder_pins": [p.name for p in c1 if p.name.startswith("PHYS_PIN_TODO_")],
        "conn1_gpio_todo": [p.name for p in c1 if p.name.startswith("GPIO_TODO_")],
        "power_physical_fanout": [
            "P48V — number of physical pins and current per pin",
            "P12V1, P12V2 — physical pin assignment and grouping",
            "P3V3 / P3V3_CONN1 — physical pins",
            "PVREF / PVREF_CONN1 — physical pins and load",
            "GND / GND_CONN1 — all return pin positions",
        ],
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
